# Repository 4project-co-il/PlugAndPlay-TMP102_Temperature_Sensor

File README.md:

# PlugAndPlay: Module with TMP102 Temperature Sensor
This is the repository with the files for PlugAndPlay module with TMP102 Temperature Sensor.

The TMP102 is accessible via the I2C channel, with ALERT pin connected to INT1 line.

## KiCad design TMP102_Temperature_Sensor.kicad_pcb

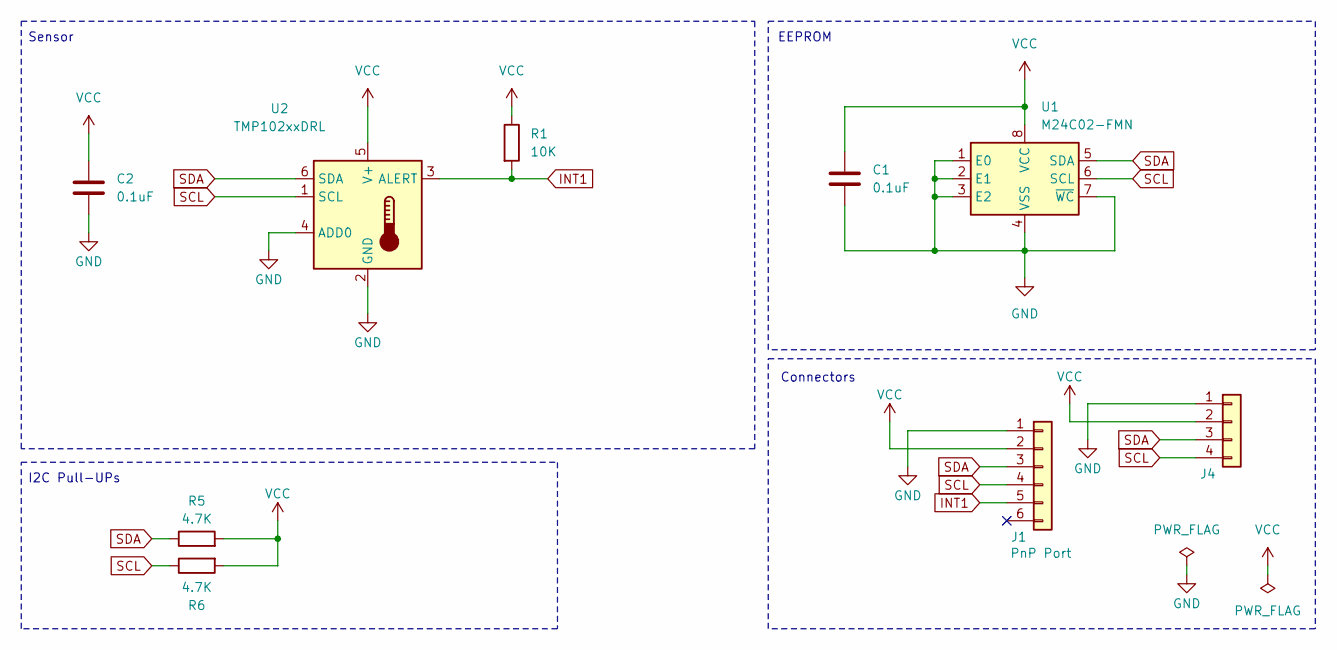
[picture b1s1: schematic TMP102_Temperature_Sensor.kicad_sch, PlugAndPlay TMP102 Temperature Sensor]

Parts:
C1, C2: 0.1uF; C_0603_1608Metric; MPN C14663
J1: JST_SH_SM06B-SRSS-TB_1x06-1MP_P1.00mm_Horizontal; MPN C7430448
J4: Conn_01x04; PogoPinsPads_1x04_P2.5mm
R1: 10K; R_0603_1608Metric_Pad0.98x0.95mm_HandSolder; MPN C25804
R5, R6: 4.7K; R_0603_1608Metric; MPN C4190
U1: M24C02-FMN; SOIC-8_3.9x4.9mm_P1.27mm; MPN C114502
U2: TMP102xxDRL; SOT-563

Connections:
GND: C1.2, C2.2, J1.1, J4.1, U1.1 (E0), U1.2 (E1), U1.3 (E2), U1.4 (VSS), U1.7 (~WC), U2.2 (GND), U2.4 (ADD0)
INT1: J1.5, R1.2, U2.3 (ALERT)
SCL: J1.4, J4.4, R6.1, U1.6 (SCL), U2.1 (SCL)
SDA: J1.3, J4.3, R5.1, U1.5 (SDA), U2.6 (SDA)
VCC: C1.1, C2.1, J1.2, J4.2, R1.1, R5.2, R6.2, U1.8 (VCC), U2.5 (V+)

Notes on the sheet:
EEPROM
Sensor
Connectors
I2C Pull-UPs

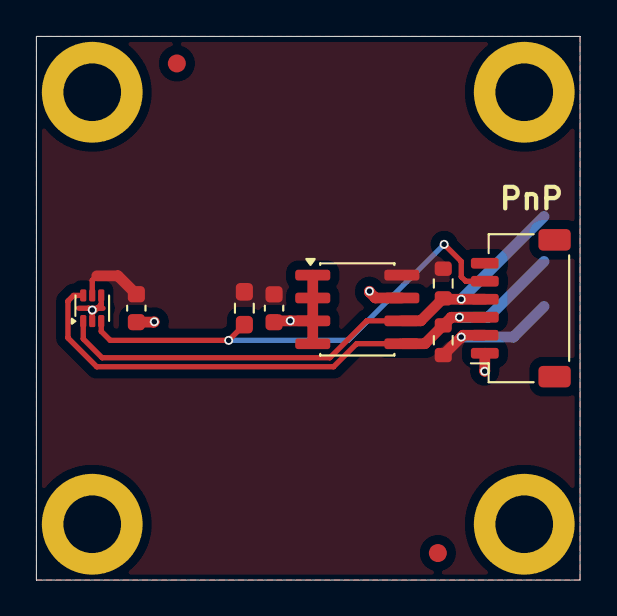
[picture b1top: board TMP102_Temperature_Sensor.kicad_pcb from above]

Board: 2 copper layers, 30.2 x 30.2 mm, 9 parts (1 on the bottom side), 5 nets.
